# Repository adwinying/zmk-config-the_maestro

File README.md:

# The Maestro

A split keyboard designed to transform your typing experience. With The Maestro, you won't just type; you'll operate your computer like conducting a symphony, effortlessly orchestrating every command with precision and flow.

## Features

- Ortholinear layout
- Split keyboard
- Built-in trackball
- 62 keys
- Low profile (2cm thickness without trackball, 3cm with)
- Fully wireless via BLE
- ZMK firmware
- A5-sized footprint when placed next to each other vertically
- Fits inside a gadget pouch when stacked on top of each other

## Parts List

| Part                                          | Quantity | Link                                                                |
| ---                                           | ---      | ---                                                                 |
| PCB top plate (left + right)                  |  1 set   |                                                                     |
| PCB middle layer (left + right)               |  1 set   |                                                                     |
| 3D printed bottom plate (left + right)        |  1 set   |                                                                     |
| 3D printed MCU cover                          |  2 pcs   |                                                                     |
| 3D printed trackball holder                   |  1 pc    |                                                                     |
| POM plastic ball (19mm diameter)              |  1 pc    | [Aliexpress](https://www.aliexpress.com/item/1005008628989005.html) |
| Nice! Nano (or compatible)                    |  2 pcs   | [Aliexpress](https://www.aliexpress.com/item/1005006271779544.html) |
| PAW3222 trackball sensor                      |  1 pc    | [Booth](https://booth.pm/ja/items/6520217)                          |
| Choc low profile switches (or compatible)     | 62 pcs   |                                                                     |
| Low profile keycaps                           | 62 pcs   |                                                                     |
| Kailh low profile hotswap sockets             | 62 pcs   | [Aliexpress](https://www.aliexpress.com/item/1005007232040760.html) |
| 1N4148W SMT diodes                            | 62 pcs   | [Aliexpress](https://www.aliexpress.com/item/1005007536859190.html) |
| 6pin 0.5mm pitch ZIF socket                   |  1 pc    | [Aliexpress](https://www.aliexpress.com/item/1005009196851411.html) |
| 6pin 0.5mm pitch FPC cable 50mm length        |  1 pc    | [Aliexpress](https://www.aliexpress.com/item/1005005590443057.html) |
| 301230 200mAh Li-ion battery                  |  2 pcs   | [Aliexpress](https://www.aliexpress.com/item/1005008666748444.html) |
| MSK-12C02 slide switches                      |  2 pcs   | [Aliexpress](https://www.aliexpress.com/item/4000685483225.html)    |
| M2 5mm cylindrical standoffs                  | 12 pcs   | [Aliexpress](https://www.aliexpress.com/item/4000152799825.html)    |
| M2 8mm cylindrical standoffs                  |  4 pcs   | [Aliexpress](https://www.aliexpress.com/item/4000152799825.html)    |
| M2 4mm flat head screws                       | 32 pcs   | [Aliexpress](https://www.aliexpress.com/item/1005005270702287.html) |
| M2 10mm flat head screws                      |  2 pcs   | [Aliexpress](https://www.aliexpress.com/item/1005005270702287.html) |
| M1.4 5mm screws                               |  3 pcs   | [Aliexpress](https://www.aliexpress.com/item/33043885403.html)      |
| Ball bearings (L x OD x ID 2mm x 4mm x 1.5mm) |  3 pcs   | [Amazon JP](https://amzn.asia/d/18Rsz2n)                            |

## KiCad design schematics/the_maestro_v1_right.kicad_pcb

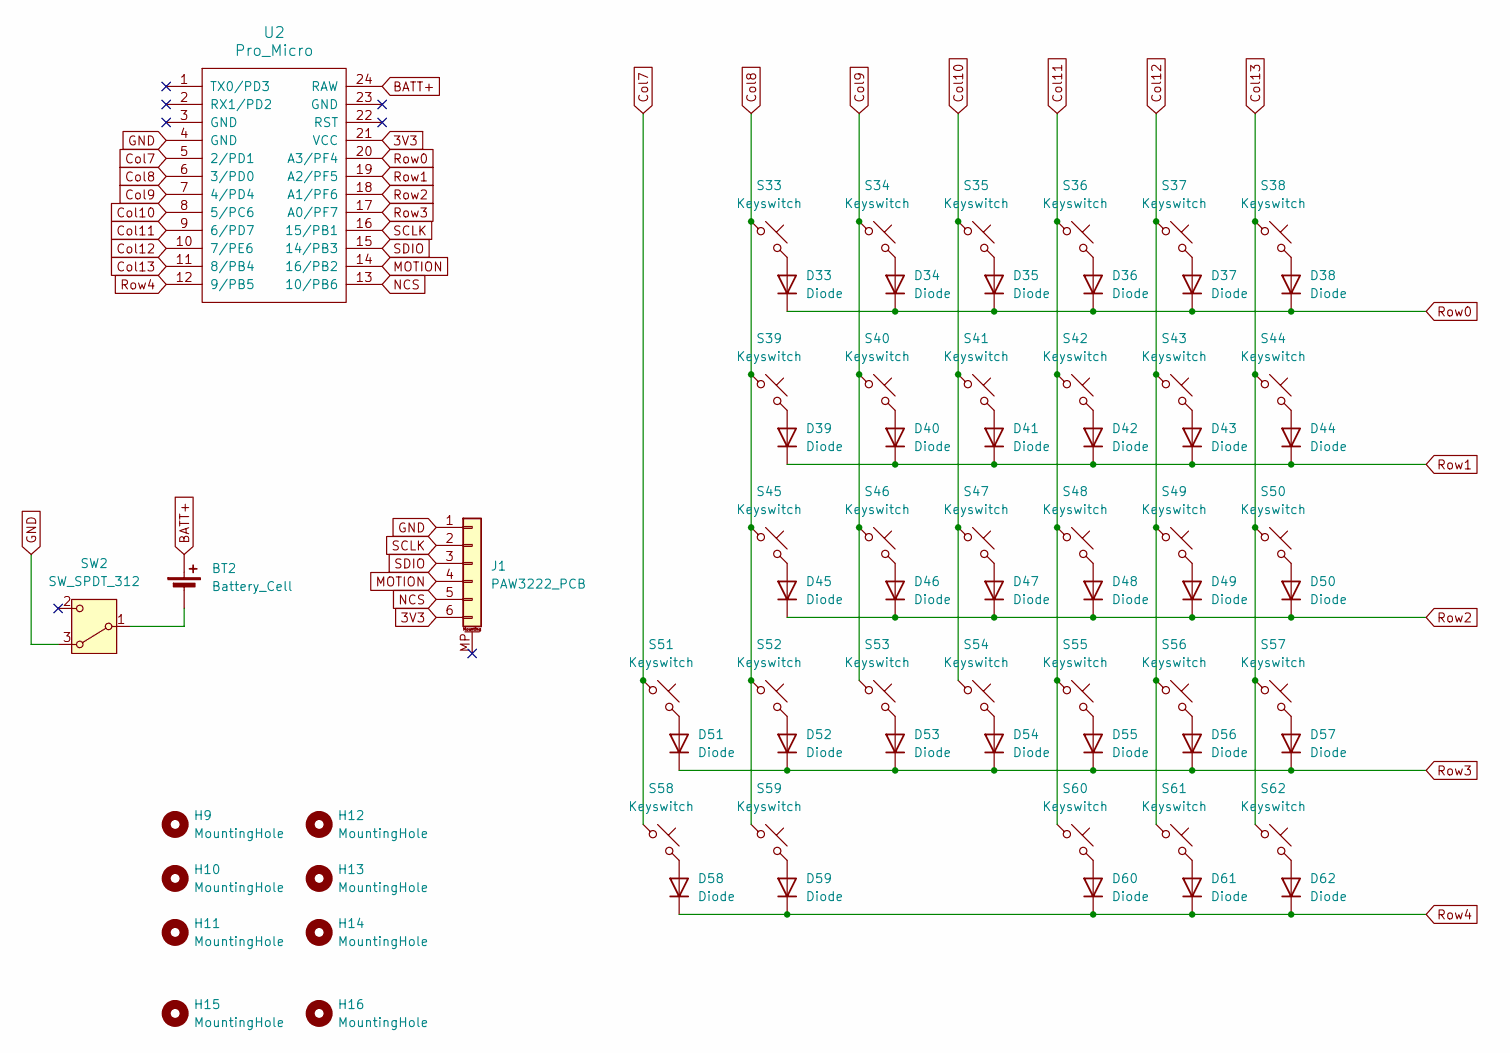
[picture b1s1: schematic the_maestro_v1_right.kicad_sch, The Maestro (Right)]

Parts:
BT2: Battery_Cell; PinHeader_1x02_P2.54mm_Vertical
D33, D34, D35, D36, D37, D38, D39, D40, D41, D42, D43, D44, D45, D46, D47, D48, D49, D50, D51, D52, D53, D54, D55, D56, D57, D58, D59, D60, D61, D62: Diode; Diode_SOD-123
H9, H10, H11, H12, H13, H14: MountingHole; MountingHole_4mm
H15, H16: MountingHole; MountingHole_2.2mm_M2
J1: PAW3222_PCB; TE_0-1734839-6_1x06-1MP_P0.5mm_Horizontal
S33, S34, S35, S36, S37, S38, S39, S40, S41, S42, S43, S44, S45, S46, S47, S48, S49, S50, S51, S52, S53, S54, S55, S56, S57, S58, S59, S60, S61, S62: Keyswitch; Hotswap_Choc_V1V2_1.00u
SW2: SW_SPDT_312; Switch_MSK12C02
U2: Pro_Micro; Arduino_Pro_Micro_Flipped

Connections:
3V3: J1.6, U2.21 (VCC)
BATT+: BT2.1 (+), U2.24 (RAW)
Col7: S51.1, S58.1, U2.5 (2/PD1)
Col8: S33.1, S39.1, S45.1, S52.1, S59.1, U2.6 (3/PD0)
Col9: S34.1, S40.1, S46.1, S53.1, U2.7 (4/PD4)
Col10: S35.1, S41.1, S47.1, S54.1, U2.8 (5/PC6)
Col11: S36.1, S42.1, S48.1, S55.1, S60.1, U2.9 (6/PD7)
Col12: S37.1, S43.1, S49.1, S56.1, S61.1, U2.10 (7/PE6)
Col13: S38.1, S44.1, S50.1, S57.1, S62.1, U2.11 (8/PB4)
GND: J1.1, SW2.3 (A), U2.4 (GND)
MOTION: J1.4, U2.14 (16/PB2)
NCS: J1.5, U2.13 (10/PB6)
unnamed: BT2.2 (-), SW2.1 (B)
unnamed: D33.2 (A), S33.2
unnamed: D34.2 (A), S34.2
unnamed: D35.2 (A), S35.2
unnamed: D36.2 (A), S36.2
unnamed: D37.2 (A), S37.2
unnamed: D38.2 (A), S38.2
unnamed: D39.2 (A), S39.2
unnamed: D40.2 (A), S40.2
unnamed: D41.2 (A), S41.2
unnamed: D42.2 (A), S42.2
unnamed: D43.2 (A), S43.2
unnamed: D44.2 (A), S44.2
unnamed: D45.2 (A), S45.2
unnamed: D46.2 (A), S46.2
unnamed: D47.2 (A), S47.2
unnamed: D48.2 (A), S48.2
unnamed: D49.2 (A), S49.2
unnamed: D50.2 (A), S50.2
unnamed: D51.2 (A), S51.2
unnamed: D52.2 (A), S52.2
unnamed: D53.2 (A), S53.2
unnamed: D54.2 (A), S54.2
unnamed: D55.2 (A), S55.2
unnamed: D56.2 (A), S56.2
unnamed: D57.2 (A), S57.2
unnamed: D58.2 (A), S58.2
unnamed: D59.2 (A), S59.2
unnamed: D60.2 (A), S60.2
unnamed: D61.2 (A), S61.2
unnamed: D62.2 (A), S62.2
Row0: D33.1 (K), D34.1 (K), D35.1 (K), D36.1 (K), D37.1 (K), D38.1 (K), U2.20 (A3/PF4)
Row1: D39.1 (K), D40.1 (K), D41.1 (K), D42.1 (K), D43.1 (K), D44.1 (K), U2.19 (A2/PF5)
Row2: D45.1 (K), D46.1 (K), D47.1 (K), D48.1 (K), D49.1 (K), D50.1 (K), U2.18 (A1/PF6)
Row3: D51.1 (K), D52.1 (K), D53.1 (K), D54.1 (K), D55.1 (K), D56.1 (K), D57.1 (K), U2.17 (A0/PF7)
Row4: D58.1 (K), D59.1 (K), D60.1 (K), D61.1 (K), D62.1 (K), U2.12 (9/PB5)
SCLK: J1.2, U2.16 (15/PB1)
SDIO: J1.3, U2.15 (14/PB3)

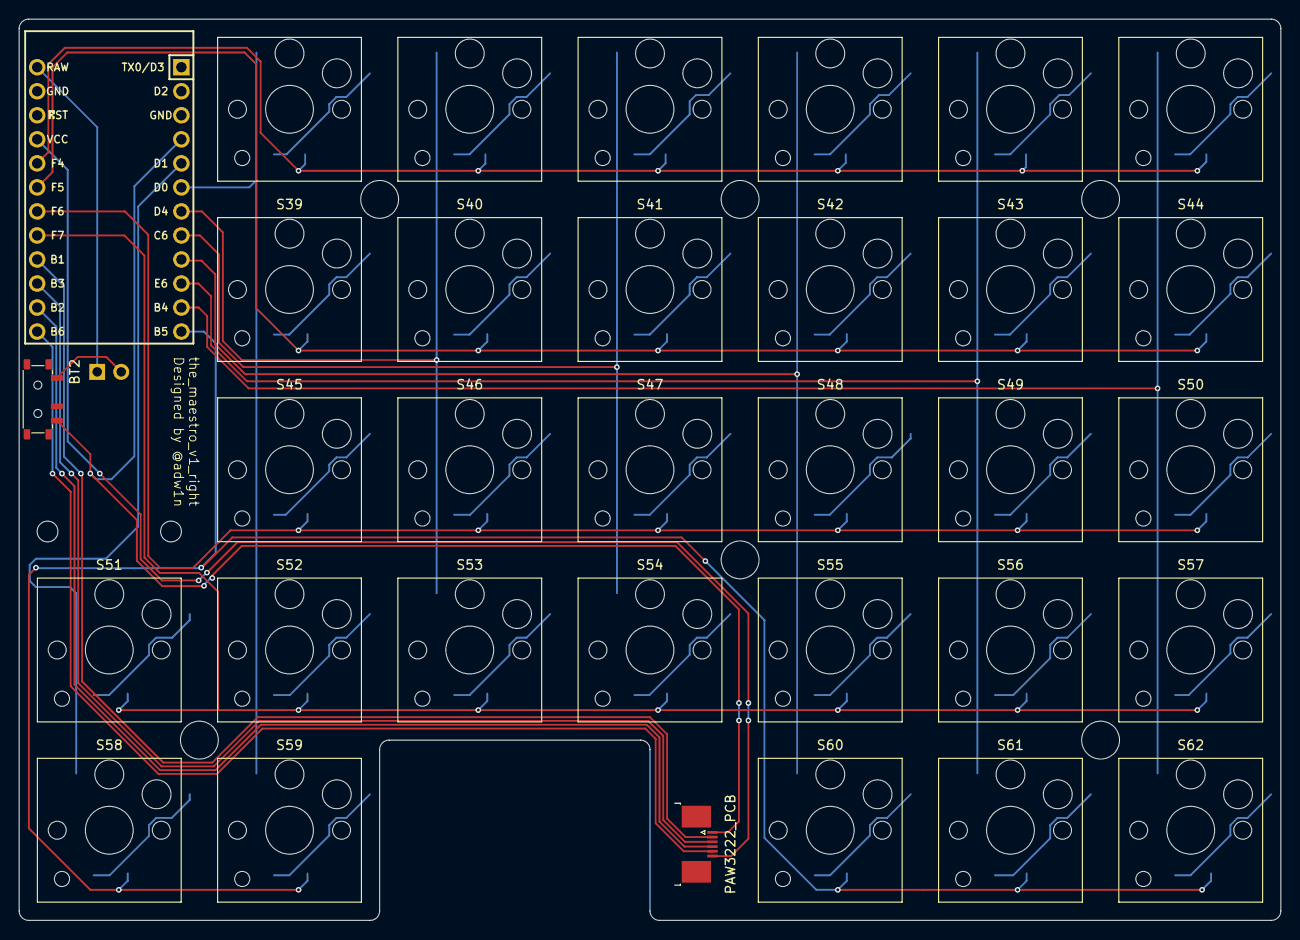
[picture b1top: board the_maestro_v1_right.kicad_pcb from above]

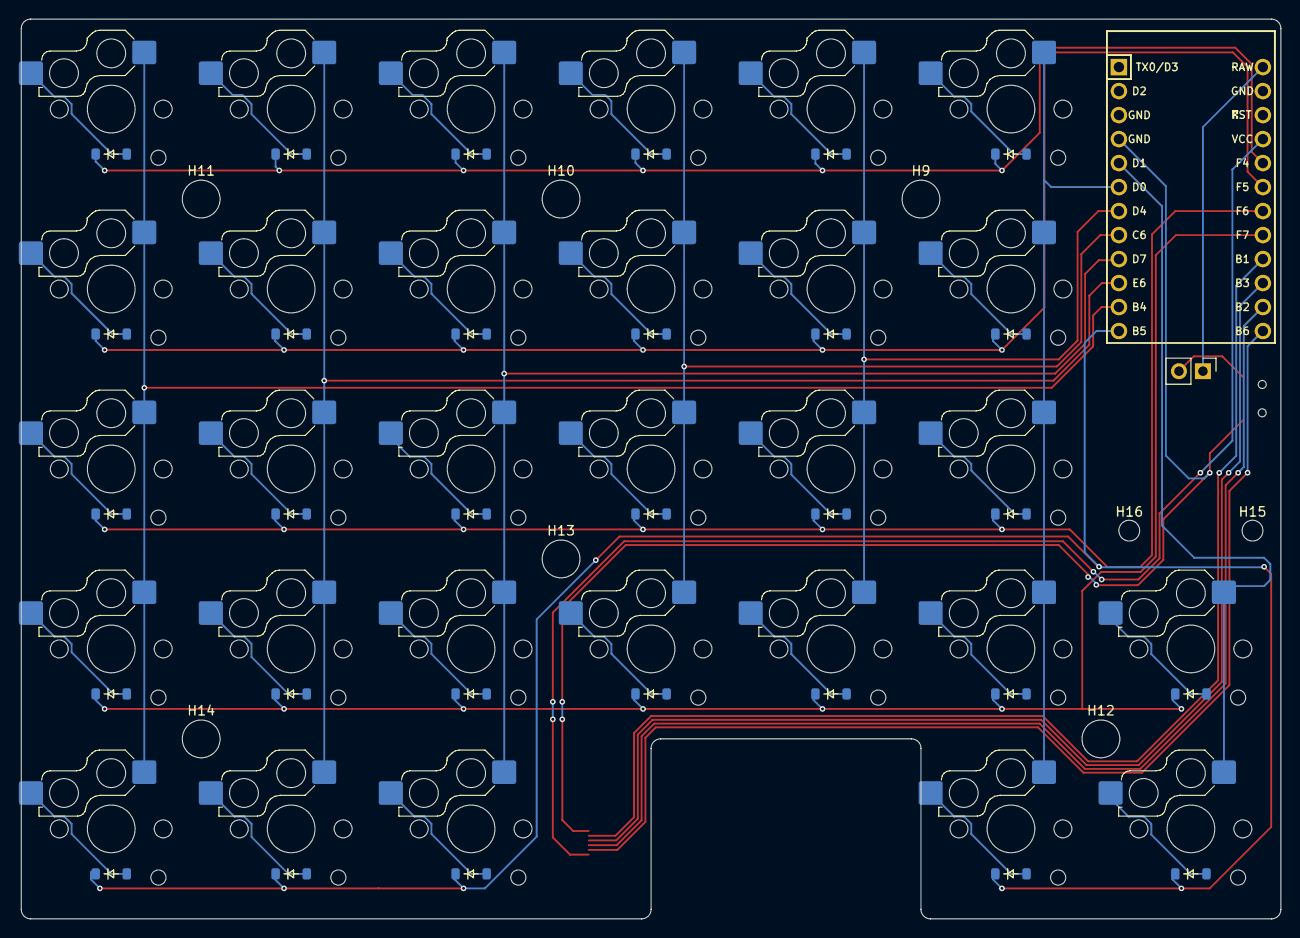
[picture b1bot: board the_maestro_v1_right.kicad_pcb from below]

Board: 2 copper layers, 133.4 x 95.2 mm, 72 parts (39 on the bottom side), 50 nets.

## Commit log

2025-06-06 Make a buildable config
2025-06-06 Initial User Config.
2025-06-07 Add PMW3610 trackball sensor
2025-06-07 Add PAW3222 trackball sensor
2025-06-07 Configure trackball behaviors
2025-06-09 Configure split layout
2025-06-10 Define keymaps
2025-06-10 Add ZMK studio support
2025-06-10 Fix zmk branch
2025-06-13 Define key combos for brackets and equal keys
2025-06-13 Change trackball sensor orientation
2025-06-22 Fix trackball pin layout
2025-06-24 Fix col 11 pin
2025-06-24 Remove multiplier
2025-06-26 Change mod-tap behavior to prioritize hold key
2025-06-26 Fix left side layer 3 trigger not working
2025-06-26 Fix layer 3 scroll not working
2025-06-26 Add reset key to keymap
2025-06-27 Move left ctrl and alt closer to thumbs
2025-06-27 Fix key right of trackball not working
2025-06-27 Add schematics
2025-06-28 Move board files to root
2025-06-28 Fix ZMK studio keyboard layout
2025-07-02 Shorten auto mouse layer timeout
2025-07-02 Add output toggle keybind
2025-07-03 Add README.md
2025-07-12 Improve battery life
2025-08-08 Move middle click key
2025-08-20 Swap position of mouse keys
